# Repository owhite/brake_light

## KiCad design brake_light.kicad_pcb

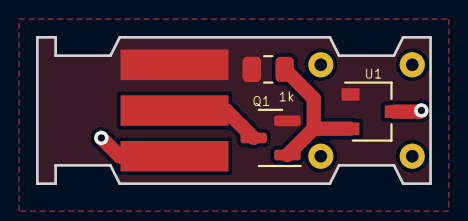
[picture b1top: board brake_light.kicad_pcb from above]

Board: 2 copper layers, 21.8 x 8.1 mm, 4 parts (0 on the bottom side), 4 nets.

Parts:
J1: Conn_01x03; 3_smd_tab
Q1: AO3401A; SOT-23
R1: 1k; R_0805_2012Metric
U1: TMAG5115; SOT-23W

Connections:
+12V: J1.1, Q1.2 (S), R1.1, U1.1 (VCC)
GND: J1.3, U1.3 (GND)
LOAD: J1.2, Q1.3 (D)
unnamed: Q1.1 (G), R1.2, U1.2 (VOUT)

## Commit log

2023-04-28 handled layout
